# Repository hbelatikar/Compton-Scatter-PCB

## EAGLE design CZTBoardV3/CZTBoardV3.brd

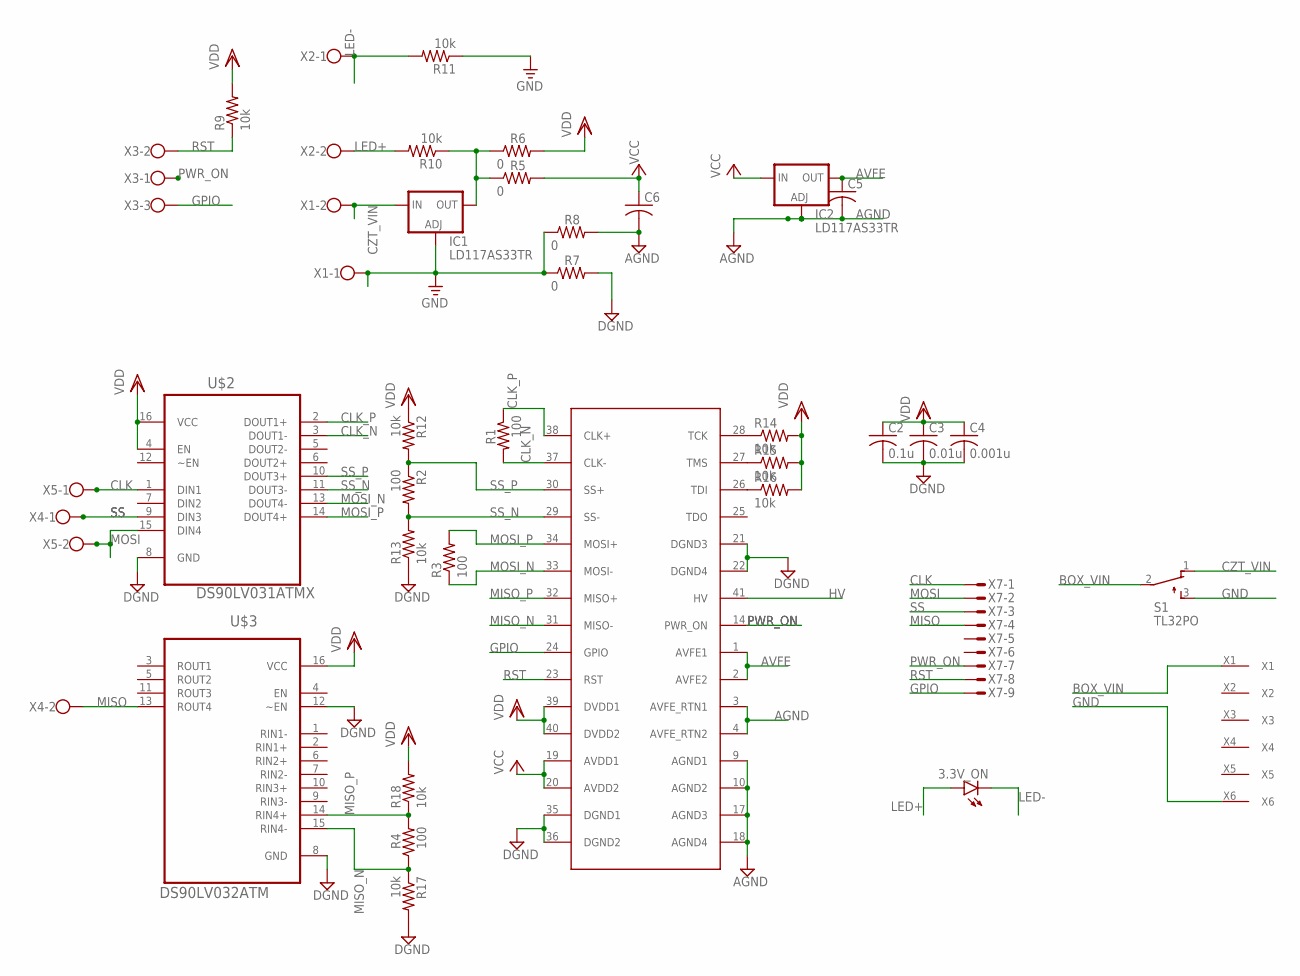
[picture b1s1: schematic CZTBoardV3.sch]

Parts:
3.3V_ON: LED3MM
C2: 0.1u; C0805K
C3: 0.01u; C0805K
C4: 0.001u; C0805K
C5, C6: C-USC0805K; C0805K
IC1, IC2: LD117AS33TR; SOT223
R1, R2, R3, R4: 100; R1206
R5, R6, R7, R8: 0; R1206
R9, R10, R11, R12, R13, R14, R15, R16, R17, R18: 10k; R1206
S1: TL32PO; TL3XPO
U$1: ORBOTECH_OMS40G256
U$2: DS90LV031ATMX; SOIC127P600X175-16N
U$3: DS90LV032ATM; SOIC127P600X175-16N
X1, X2, X4, X5: W237-102
X3: W237-103
X6: GX16
X7: M09VS; M09V

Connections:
3.3VREG: IC1.4 (OUT), R5.1, R6.1, R10.1
AGND: C5.2, C6.2, IC2.1 (ADJ), R8.2, U$1.3 (AVFE_RTN1), U$1.4 (AVFE_RTN2), U$1.9 (AGND1), U$1.10 (AGND2), U$1.17 (AGND3), U$1.18 (AGND4)
AVFE: C5.1, IC2.4 (OUT), U$1.1 (AVFE1), U$1.2 (AVFE2)
BOX_VIN: S1.2, X6.X1
CLK: U$2.1 (DIN1), X5.1, X7.1
CLK_N: R1.2, U$1.37 (CLK-), U$2.3 (DOUT1-)
CLK_P: R1.1, U$1.38 (CLK+), U$2.2 (DOUT1+)
CZT_VIN: IC1.3 (IN), S1.1 (O), X1.2
DGND: C2.2, C3.2, C4.2, R7.2, R13.1, R17.2, U$1.21 (DGND3), U$1.22 (DGND4), U$1.35 (DGND1), U$1.36 (DGND2), U$2.8 (GND), U$3.8 (GND), U$3.12 (~EN)
GND: IC1.1 (ADJ), R7.1, R8.1, R11.1, S1.3 (S), X1.1, X6.X6
GPIO: U$1.24 (GPIO), X3.3, X7.9
HV: U$1.41 (HV)
LED+: 3.3V_ON.A, R10.2, X2.2
LED-: 3.3V_ON.K (C), R11.2, X2.1
MISO: U$3.13 (ROUT4), X4.2, X7.4
MISO_N: R4.1, R17.1, U$1.31 (MISO-), U$3.15 (RIN4-)
MISO_P: R4.2, R18.1, U$1.32 (MISO+), U$3.14 (RIN4+)
MOSI: U$2.15 (DIN4), X5.2, X7.2
MOSI_N: R3.1, U$1.33 (MOSI-), U$2.13 (DOUT4-)
MOSI_P: R3.2, U$1.34 (MOSI+), U$2.14 (DOUT4+)
unnamed: R14.1, U$1.28 (TCK)
unnamed: R15.1, U$1.27 (TMS)
unnamed: R16.1, U$1.26 (TDI)
PWR_ON: U$1.14 (PWR_ON), X3.1, X7.7
RST: R9.1, U$1.23 (RST), X3.2, X7.8
SS: U$2.9 (DIN3), X4.1, X7.3
SS_N: R2.2, R13.2, U$1.29 (SS-), U$2.11 (DOUT3-)
SS_P: R2.1, R12.2, U$1.30 (SS+), U$2.10 (DOUT3+)
VCC: C6.1, IC2.3 (IN), R5.2, U$1.19 (AVDD1), U$1.20 (AVDD2)
VDD: C2.1, C3.1, C4.1, R6.2, R9.2, R12.1, R14.2, R15.2, R16.2, R18.2, U$1.39 (DVDD1), U$1.40 (DVDD2), U$2.4 (EN), U$2.16 (VCC), U$3.16 (VCC)

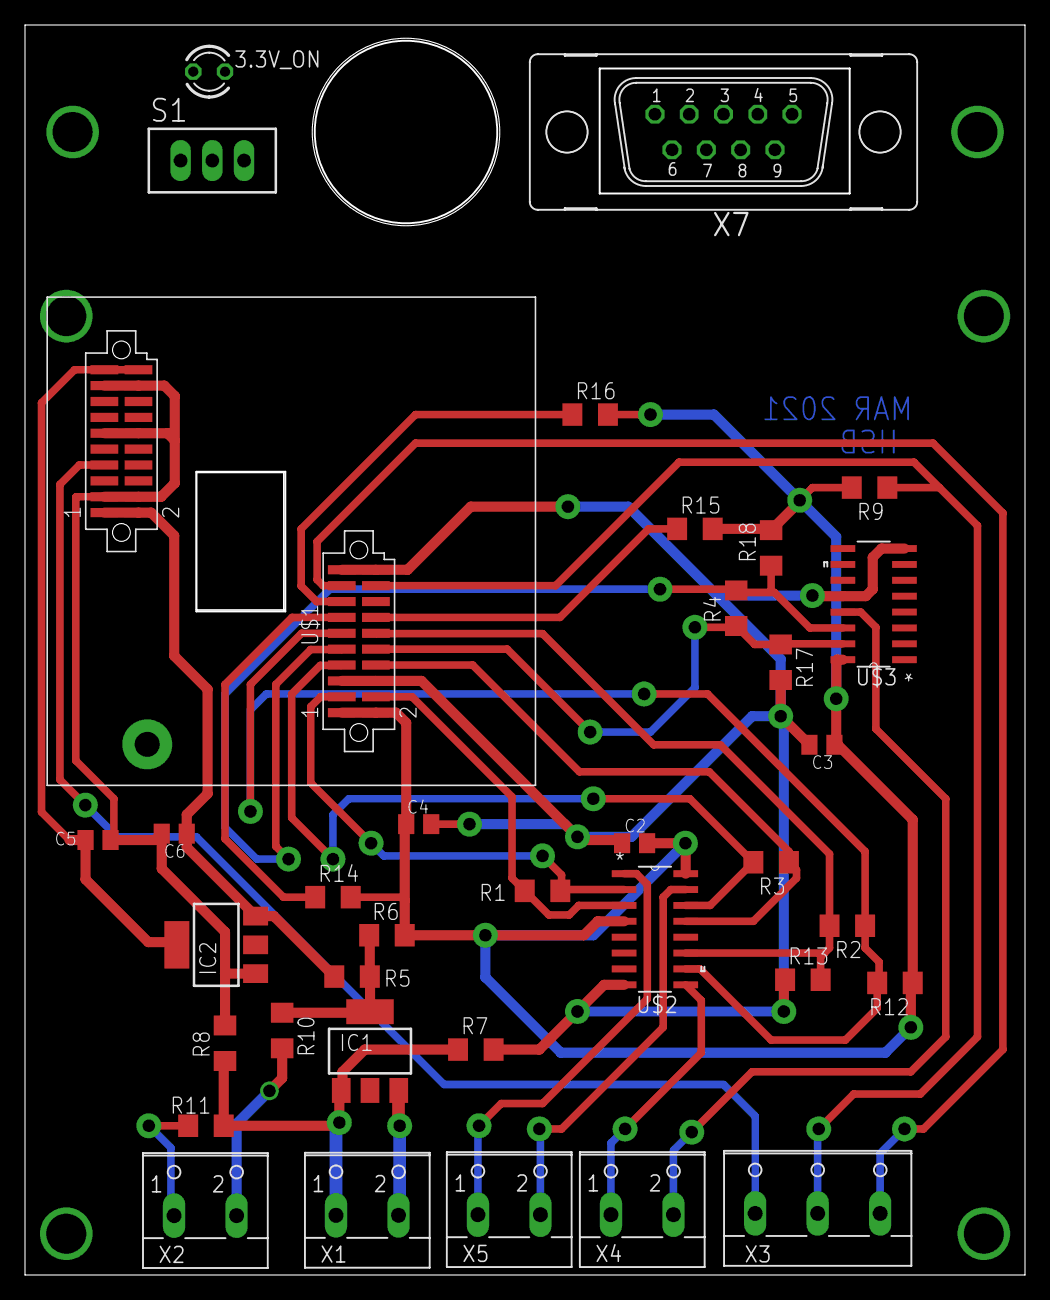
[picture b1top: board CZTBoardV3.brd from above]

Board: 2 copper layers, 79.8 x 99.8 mm, 37 parts (0 on the bottom side), 29 nets.

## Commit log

2021-07-22 Updated to final design and created output paths
2021-08-10 some changes
